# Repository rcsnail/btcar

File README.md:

# btcar

Kasuta Zadig https://zadig.akeo.ie/ tarkvara paigaldamaks USBasp programmaatorile WinUSB draiver.

flash_usbasp.bat kirjutab bootloaderi koos btcar tarkvaraga Atmeli mikroprotsessorisse.

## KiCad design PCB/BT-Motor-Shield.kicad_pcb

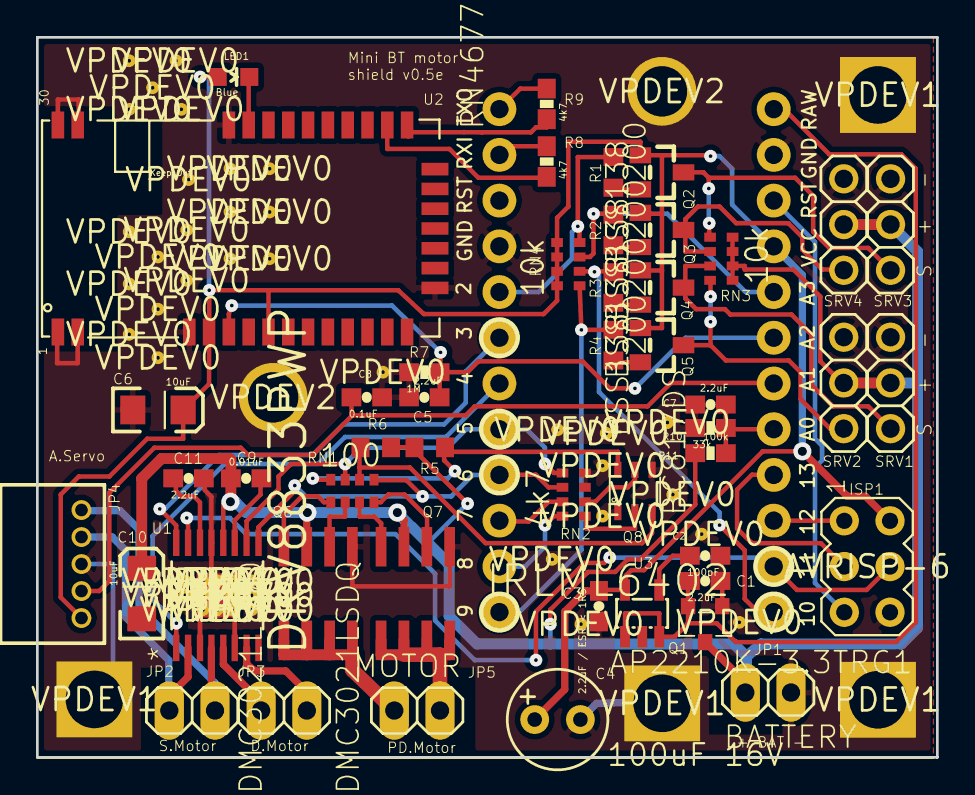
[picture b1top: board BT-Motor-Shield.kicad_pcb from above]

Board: 2 copper layers, 50.0 x 40.0 mm, 100 parts (0 on the bottom side), 51 nets.

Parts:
C1, C5, C7, C11: 2.2uF; 0603-CAP
C2: 100pF; 0603-CAP
C3: 2.2uF / ESR < 1R5; 0603-CAP
C4: 100uF 16V; E2,5-6
C6, C10: 10uF; EIA3216
C8: 0.1uF; 0603-CAP
C9: 0.01uF; 0603-CAP
ISP1: AVRISP-6; AVRISP
JP1: BATTERY; 1X02
JP2, JP3: 1X02
JP4: S5B-ZR
JP5: MOTOR; 1X02
JP6, JP7: 1X12
LED1: Blue; 0603-LED-ALT1
Q1: IRLML6402; MICRO3
Q2, Q3, Q4, Q5: BSS138; SOT23
Q6, Q7: DMC3021LSDQ; SO8
Q8: BC817DS; SMT6
R1, R2, R3, R4: 200; R0603
R5, R6: 470; R0603
R7: 1M; 0603-RES
R8, R9: 4k7; 0603-RES
R10: 33k; 0603-RES
R11: 100k; 0603-RES
RN1: 100; 0603-ARC
RN2: 4k7; 0603-ARC
RN3, RN4: 10k; 0603-ARC
SRV1, SRV2, SRV3, SRV4: 1X03
U1: DRV8833PWP; HTSSOP-16
U2: RN4677; BM77_BIG
U3: AP2210K-3.3TRG1; SOT25
VP_0, VP_1, VP_2, VP_3, VP_4, VP_5, VP_6, VP_7, VP_8, VP_9, VP_10, VP_11, VP_12, VP_13, VP_14, VP_15, VP_16, VP_17, VP_20, VP_21, VP_22, VP_23, VP_24, VP_25, VP_26, VP_27, VP_28, VP_29, VP_30, VP_31, VP_32, VP_33, VP_34, VP_35, VP_36, VP_37, VP_38, VP_41, VP_42, VP_43, VP_44, VP_45, VP_46, VP_47: VPDEV0; VPAC0
VP_18, VP_39, VP_39#2, VP_39#3: VPDEV1; VPAC1
VP_19, VP_40: VPDEV2; VPAC2

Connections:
3.3V: C3.1, C4.+, C6.A, ISP1.2, JP4.5, JP6.4, LED1.A, Q2.1, Q3.1, Q4.1, Q5.1, RN4.5, RN4.6, RN4.7, RN4.8, U2.BAT_, U2.VDD_, U3.5
A0: C7.1, JP6.8, R10.2, R11.1
A1: C8.1, JP4.4, JP6.7
A2: C5.1, JP6.6, R7.2, U2.SW_B
A3: JP6.5, R2.2, RN4.3
B+: C9.2, C10.A, JP1.1, Q1.3, Q6.3, Q7.3, R5.2, R6.2, R11.2, RN3.5, RN3.6, RN3.7, RN3.8, SRV1.2, SRV2.2, SRV3.2, SRV4.2, U1.12
D2: JP7.8, R1.2, RN4.4
D3: JP7.7, U1.16
D4: JP7.6, U1.1
D5: JP7.5, RN1.7, RN2.5, U1.10
D6: JP7.4, RN1.5, RN2.6, U1.9
D7: JP7.3, RN2.7
D8: JP7.2, RN2.8
D9: JP7.1, R4.2, RN4.1
D10: JP6.12, R3.2, RN4.2
GND: C1.2, C2.2, C3.2, C4.-, C5.2, C6.C, C7.2, C8.2, C10.C, C11.2, ISP1.6, JP1.2, JP4.3, JP6.2, JP7.9, Q1.1, Q6.1, Q7.1, Q8.1, Q8.4, R7.1, R10.1, RN2.3, RN2.4, SRV1.3, SRV2.3, SRV3.3, SRV4.3, U1.3, U1.6, U1.13, U1.17, U2.GND1, U2.GND2, U2.GND3, U2.GND4, U2.GND5, U2.GND6, U2.P17/, U3.2, VP_0.VP, VP_1.VP, VP_2.VP, VP_3.VP, VP_4.VP, VP_5.VP, VP_6.VP, VP_7.VP, VP_8.VP, VP_9.VP, VP_10.VP, VP_11.VP, VP_12.VP, VP_13.VP, VP_14.VP, VP_15.VP, VP_16.VP, VP_17.VP, VP_18.VP, VP_19.VP, VP_20.VP, VP_21.VP, VP_22.VP, VP_23.VP, VP_24.VP, VP_25.VP, VP_26.VP, VP_27.VP, VP_28.VP, VP_29.VP, VP_30.VP, VP_31.VP, VP_32.VP, VP_33.VP, VP_34.VP, VP_35.VP, VP_36.VP, VP_37.VP, VP_38.VP, VP_39.VP, VP_39#2.VP, VP_39#3.VP, VP_40.VP, VP_41.VP, VP_42.VP, VP_43.VP, VP_44.VP, VP_45.VP, VP_46.VP, VP_47.VP
MISO: ISP1.1, JP6.10
MOSI: ISP1.4, JP6.11, U1.15
unnamed: C2.1, U3.4
unnamed: C9.1, U1.11
unnamed: C11.1, U1.14
unnamed: JP2.1, JP4.2, U1.2
unnamed: JP2.2, JP4.1, U1.4
unnamed: JP3.1, U1.5
unnamed: JP3.2, U1.7
unnamed: JP5.1, Q7.5, Q7.6, Q7.7, Q7.8
unnamed: JP5.2, Q6.5, Q6.6, Q6.7, Q6.8
unnamed: LED1.C, U2.LED1
unnamed: Q2.2, R1.1
unnamed: Q2.3, RN3.1, SRV3.1
unnamed: Q3.2, R2.1
unnamed: Q3.3, RN3.2, SRV4.1
unnamed: Q4.2, R3.1
unnamed: Q4.3, RN3.3, SRV1.1
unnamed: Q5.2, R4.1
unnamed: Q5.3, RN3.4, SRV2.1
unnamed: Q6.2, RN1.2
unnamed: Q6.4, RN1.1
unnamed: Q7.2, RN1.4
unnamed: Q7.4, RN1.3
unnamed: Q8.2, RN2.1
unnamed: Q8.3, R6.1, RN1.6
unnamed: Q8.5, RN2.2
unnamed: Q8.6, R5.1, RN1.8
unnamed: R8.1, U2.TXD
unnamed: R9.1, U2.RXD
RAW: C1.1, JP6.1, Q1.2, U3.1, U3.3
RESET2: ISP1.5, JP6.3
RXI: JP7.11, R8.2
SCK: ISP1.3, JP6.9
TXO: JP7.12, R9.2

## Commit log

2018-02-08 First commit. Work in progress.
2018-02-14 Renamed source folder to RCSnail.
    Added boards/packages json file
2019-03-05 Flashing Arduino from command line without make
2019-03-05 USBasp programmaatori kasutamise instruktsioonid
2021-01-29 Auto elektroonika trükkplaadi esimese versiooni KiCAD projekt
